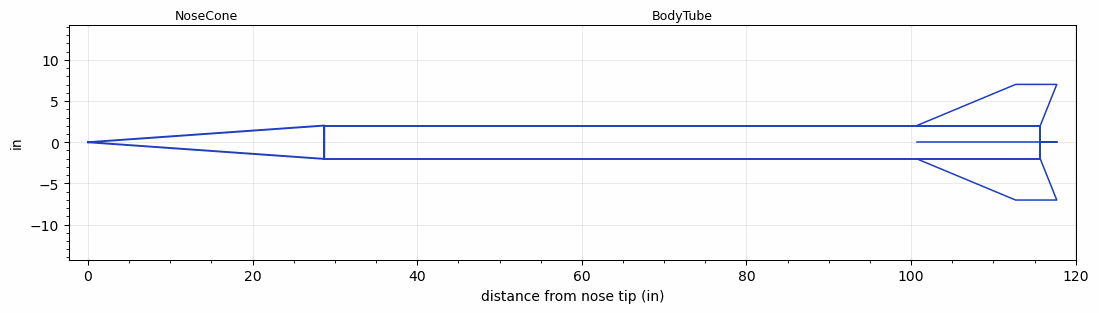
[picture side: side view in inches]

<RASAeroDocument>
 <FileVersion>2</FileVersion>
 <RocketDesign>
  <NoseCone>
   <Length>28.6999</Length>
   <Diameter>4.05</Diameter>
   <Shape>Conical</Shape>
   <BluntRadius>0.02</BluntRadius>
   <Location>0</Location>
  </NoseCone>
  <BodyTube>
   <Length>87</Length>
   <Diameter>4.05</Diameter>
   <Location>28.6999</Location>
   <Fin>
    <Count>4</Count>
    <Chord>15</Chord>
    <Span>5</Span>
    <SweepDistance>12</SweepDistance>
    <TipChord>5</TipChord>
    <Thickness>0.25</Thickness>
    <LERadius>0.02</LERadius>
    <Location>15</Location>
    <AirfoilSection>Hexagonal</AirfoilSection>
    <FX1>2</FX1>
    <FX3>2</FX3>
   </Fin>
  </BodyTube>
  <Surface>Camouflage Paint</Surface>
  <ModifiedBarrowman>True</ModifiedBarrowman>
  <Turbulence>True</Turbulence>
  <UseBooster1>False</UseBooster1>
  <UseBooster2>False</UseBooster2>
 </RocketDesign>
 <LaunchSite>
  <Altitude>2000</Altitude>
  <Pressure>29.92</Pressure>
  <RodAngle>0</RodAngle>
  <RodLength>20</RodLength>
  <Temperature>85</Temperature>
  <WindSpeed>4.47</WindSpeed>
 </LaunchSite>
 <Recovery>
  <Altitude1>0</Altitude1>
  <Altitude2>0</Altitude2>
  <DeviceType1>None</DeviceType1>
  <DeviceType2>None</DeviceType2>
  <Event1>False</Event1>
  <Event2>False</Event2>
  <Size1>0</Size1>
  <Size2>0</Size2>
  <EventType1>None</EventType1>
  <EventType2>None</EventType2>
  <CD1>0</CD1>
  <CD2>0</CD2>
 </Recovery>
 <SimulationList>
  <Simulation>
   <SustainerEngine>P9629FB(NC)  (Polaris)</SustainerEngine>
   <SustainerLaunchWt>66</SustainerLaunchWt>
   <SustainerNozzleDiameter>4</SustainerNozzleDiameter>
   <SustainerCG>62.59</SustainerCG>
   <SustainerIgnitionDelay>0</SustainerIgnitionDelay>
   <Booster1SeparationDelay>0</Booster1SeparationDelay>
   <Booster1IgnitionDelay>0</Booster1IgnitionDelay>
   <IncludeBooster1>False</IncludeBooster1>
   <Booster2Delay>0</Booster2Delay>
   <IncludeBooster2>False</IncludeBooster2>
   <TimetoApogee>153.1251</TimetoApogee>
   <MaxAltitude>383204.6</MaxAltitude>
   <MaxVelocity>8404.265</MaxVelocity>
  </Simulation>
 </SimulationList>
</RASAeroDocument>
